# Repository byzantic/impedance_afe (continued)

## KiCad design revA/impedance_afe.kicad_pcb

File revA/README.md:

> **Superseded by Rev B** (repo root). These Rev A files were converted to KiCad 9/10 in commit 697954e.
> The scripts in `revA/scripts/` write KiCad 7 files and would overwrite that conversion. Keep them for reference only.

# Impedance / C-V / DLTS / Electrochem AFE — Rev A (generated)

Fabrication outputs (Gerbers, JLCPCB BOM/CPL, schematic PDF, renders) are attached to each [GitHub Release](../../releases), not stored in the repo.

KiCad 7 format (opens in KiCad 8/9, which will offer to upgrade the files). 2-layer, 150 × 110 mm, 1.6 mm FR4, JLCPCB rules (0.25 mm default track/clearance, 0.6/0.3 mm vias).

## Architecture
| Block | Parts | Function |
|---|---|---|
| Power | J1, D1/D2, FB1/FB2, U8 | External ±15 V (bench supply), Schottky reverse protection, ferrite + bulk filtering, 78M05 → +5 V for relays and logic |
| Drive | J2 → R3 → U1 (OPA828), R4 → J3 (CE) | **Device mode** (K6 on): U1 is a follower, CE = VIN, RE senses the DUT. **Potentiostat** (K7 on, K6 off): PI loop, R5 = 10k, C9 = 100p, R6 = 1k zero, drives CE so that V_RE = VIN |
| RE / guard | J4 → R7 → U2 (electrometer follower), U3 → R9 → J5 and the J4 shell | Driven guard on the RE cable shield and the GUARD BNC; RE_BUF copper guard around U2's input |
| V monitor | R10/R11 (0.1 %) → U4 → J6 | V_OUT = V_RE / 2, back-terminated in 49.9 Ω |
| Hi-gain TIA | J7 (WE) → U5, R21–R25 ∥ C21–C25, K1–K5 | Virtual ground on WE. Ranges 10k / 100k / 1M / 10M / 100M (±5 V full scale = 500 µA … 50 nA). Relays sit on the output side, so off-relay leakage shows up as a gain error, not an offset |
| Lo-gain TIA | D3 (BAV199 antiparallel) → U6, R15 = 499 Ω ∥ 68 p | Above about V_sat/R_f, U5 saturates, WE rises about 0.6 V and the current diverts to U6 (10 mA full scale). Needs no sync and adds no charge injection |
| Control | J10 → U7 (74HCT541) → coils, D11–D18 | High-side coil drive, so off coils sit at 0 V (keeps coil-to-contact leakage out of the summing node) |

Output polarity: I_HI = −I_WE·R_f and I_LO = −I_WE·499 Ω, where I_WE is current flowing *into* the WE terminal.

## GPIO header J10 (3.3 V logic OK; 100k pulls to +5 V or GND)
| Pin | Signal | Relay | Default |
|---|---|---|---|
| 1 | CTL1 | K1 10k range | off |
| 2 | CTL2 | K2 100k | off |
| 3 | CTL3 | K3 1M | **on** |
| 4 | CTL4 | K4 10M | off |
| 5 | CTL5 | K5 100M | off |
| 6 | CTL6 | K6 DEV (follower) | **on** |
| 7 | CTL7 | K7 PSTAT (PI loop) | off |
| 8 | CTL8 | K8 RE_LOCAL (RE tied to CE on the board) | **on** |
| 9, 10 | GND | | |
Exactly one range should be on at a time; use break-before-make, ~2 ms. Keep ≤ 4 coils on at once (74HCT541 Icc limit). For potentiostat mode: CTL6 = 0, CTL7 = 1, CTL8 = 0.

## Verification status
- Netlist: the KiCad-exported netlist was checked against the design intent by script (69 nets, 0 mismatches). **KiCad's own ERC was not run** (KiCad 7 has no headless ERC). Run ERC in KiCad before ordering.
- PCB DRC (KiCad 7): 0 clearance errors, 0 unconnected. The remaining items are cosmetic silkscreen overlaps/edge clips and "footprint not in library table" notices.
- Not simulated. Loop stability (especially the PI potentiostat with a real cell) and the TIA compensation values are first-pass hand calculations.

## Things to check / known limitations
1. **Reed relay pinout** assumes Standex/Meder SIL: pins 1 and 7 are the contact, pins 3 and 5 are the coil. Confirm against the datasheet of the part you buy.
2. Generic SIP-1A05 insulation is specified at only ≥1e10 Ω. That is up to ~1 % gain error on the 100M range (calibrate it out), or fit Coto 9007 / Pickering parts (≥1e12) on K4/K5.
3. During a DLTS fill pulse the WE node sits about 0.6 V off ground (diode drop), so the DUT voltage is lower by that amount while I_LO is active.
4. At 1 MHz C-V, expect a few degrees of phase shift in the V and I chains. Calibrate with reference R/C loads (open/short/load) for C-V.
5. PI compensation (C9/R6) and C26 may need tuning for your cells and cables.
6. Most passives have no LCSC numbers. Use JLC's BOM matcher. Verified: OPA828IDR = C1850247, reed relay = C7316298. The 100 MΩ (R25) and 0.47 pF (C24) values may need sourcing.
7. The BNC footprint is the Amphenol B6252HB right-angle. Check that your BNCs match its pin pattern. JLC CPL rotations for SOT-23/SOIC may need fixing in the JLC preview.
8. The pull-ups go to +5 V. With a 3.3 V MCU high, about 17 µA flows into the GPIO clamp (harmless for most MCUs). Fit 3.3 V-referenced pull-ups if you prefer.
9. The pulse-sync input is not needed with diode steering, so none was fitted.

## Regenerating
Everything comes from `scripts/design.py`. Run the scripts from the repo root with KiCad 7's Python (`pcbnew`) and Freerouting. `route.py` expects the jar at `/root/tools/fr.jar`, so edit that path first.
```
python3 scripts/gen_sch.py          # schematic + sym_uuid.json
kicad-cli sch export netlist -o afe.net impedance_afe.kicad_sch && python3 scripts/check_net.py
PASSES=80 bash scripts/build_pcb.sh # place, pre-route critical nets, autoroute, clean up
```
Note: the autoroute pass is not deterministic. The board in this repo is the checked result; regenerating will change the routing.

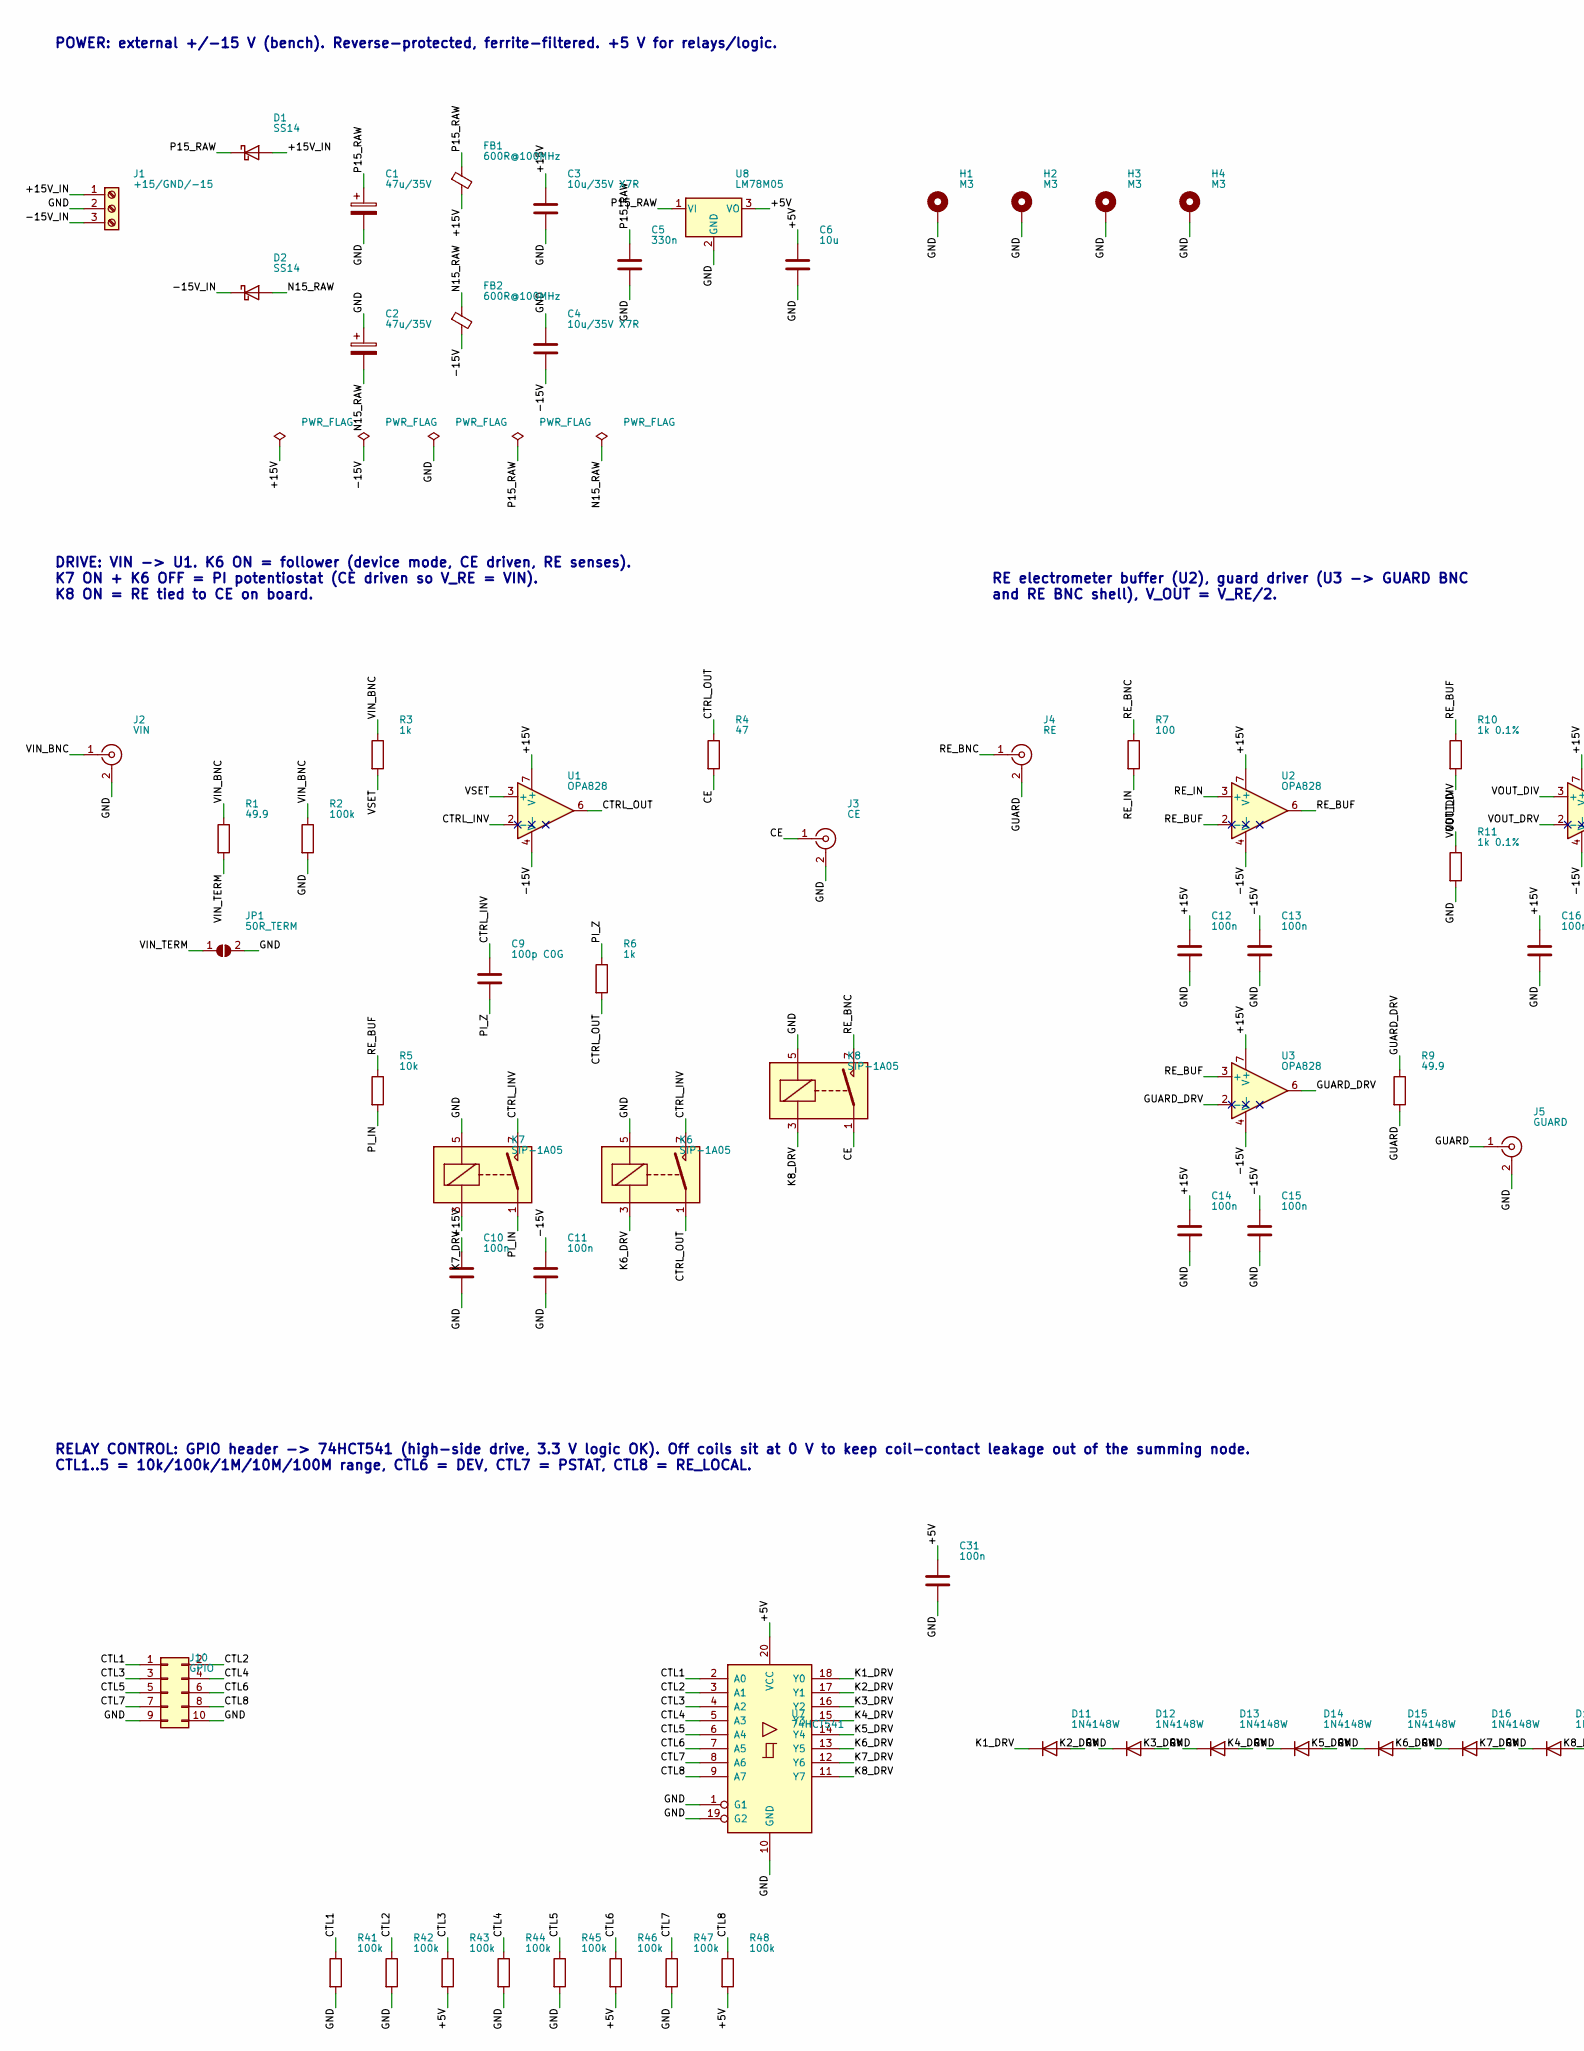
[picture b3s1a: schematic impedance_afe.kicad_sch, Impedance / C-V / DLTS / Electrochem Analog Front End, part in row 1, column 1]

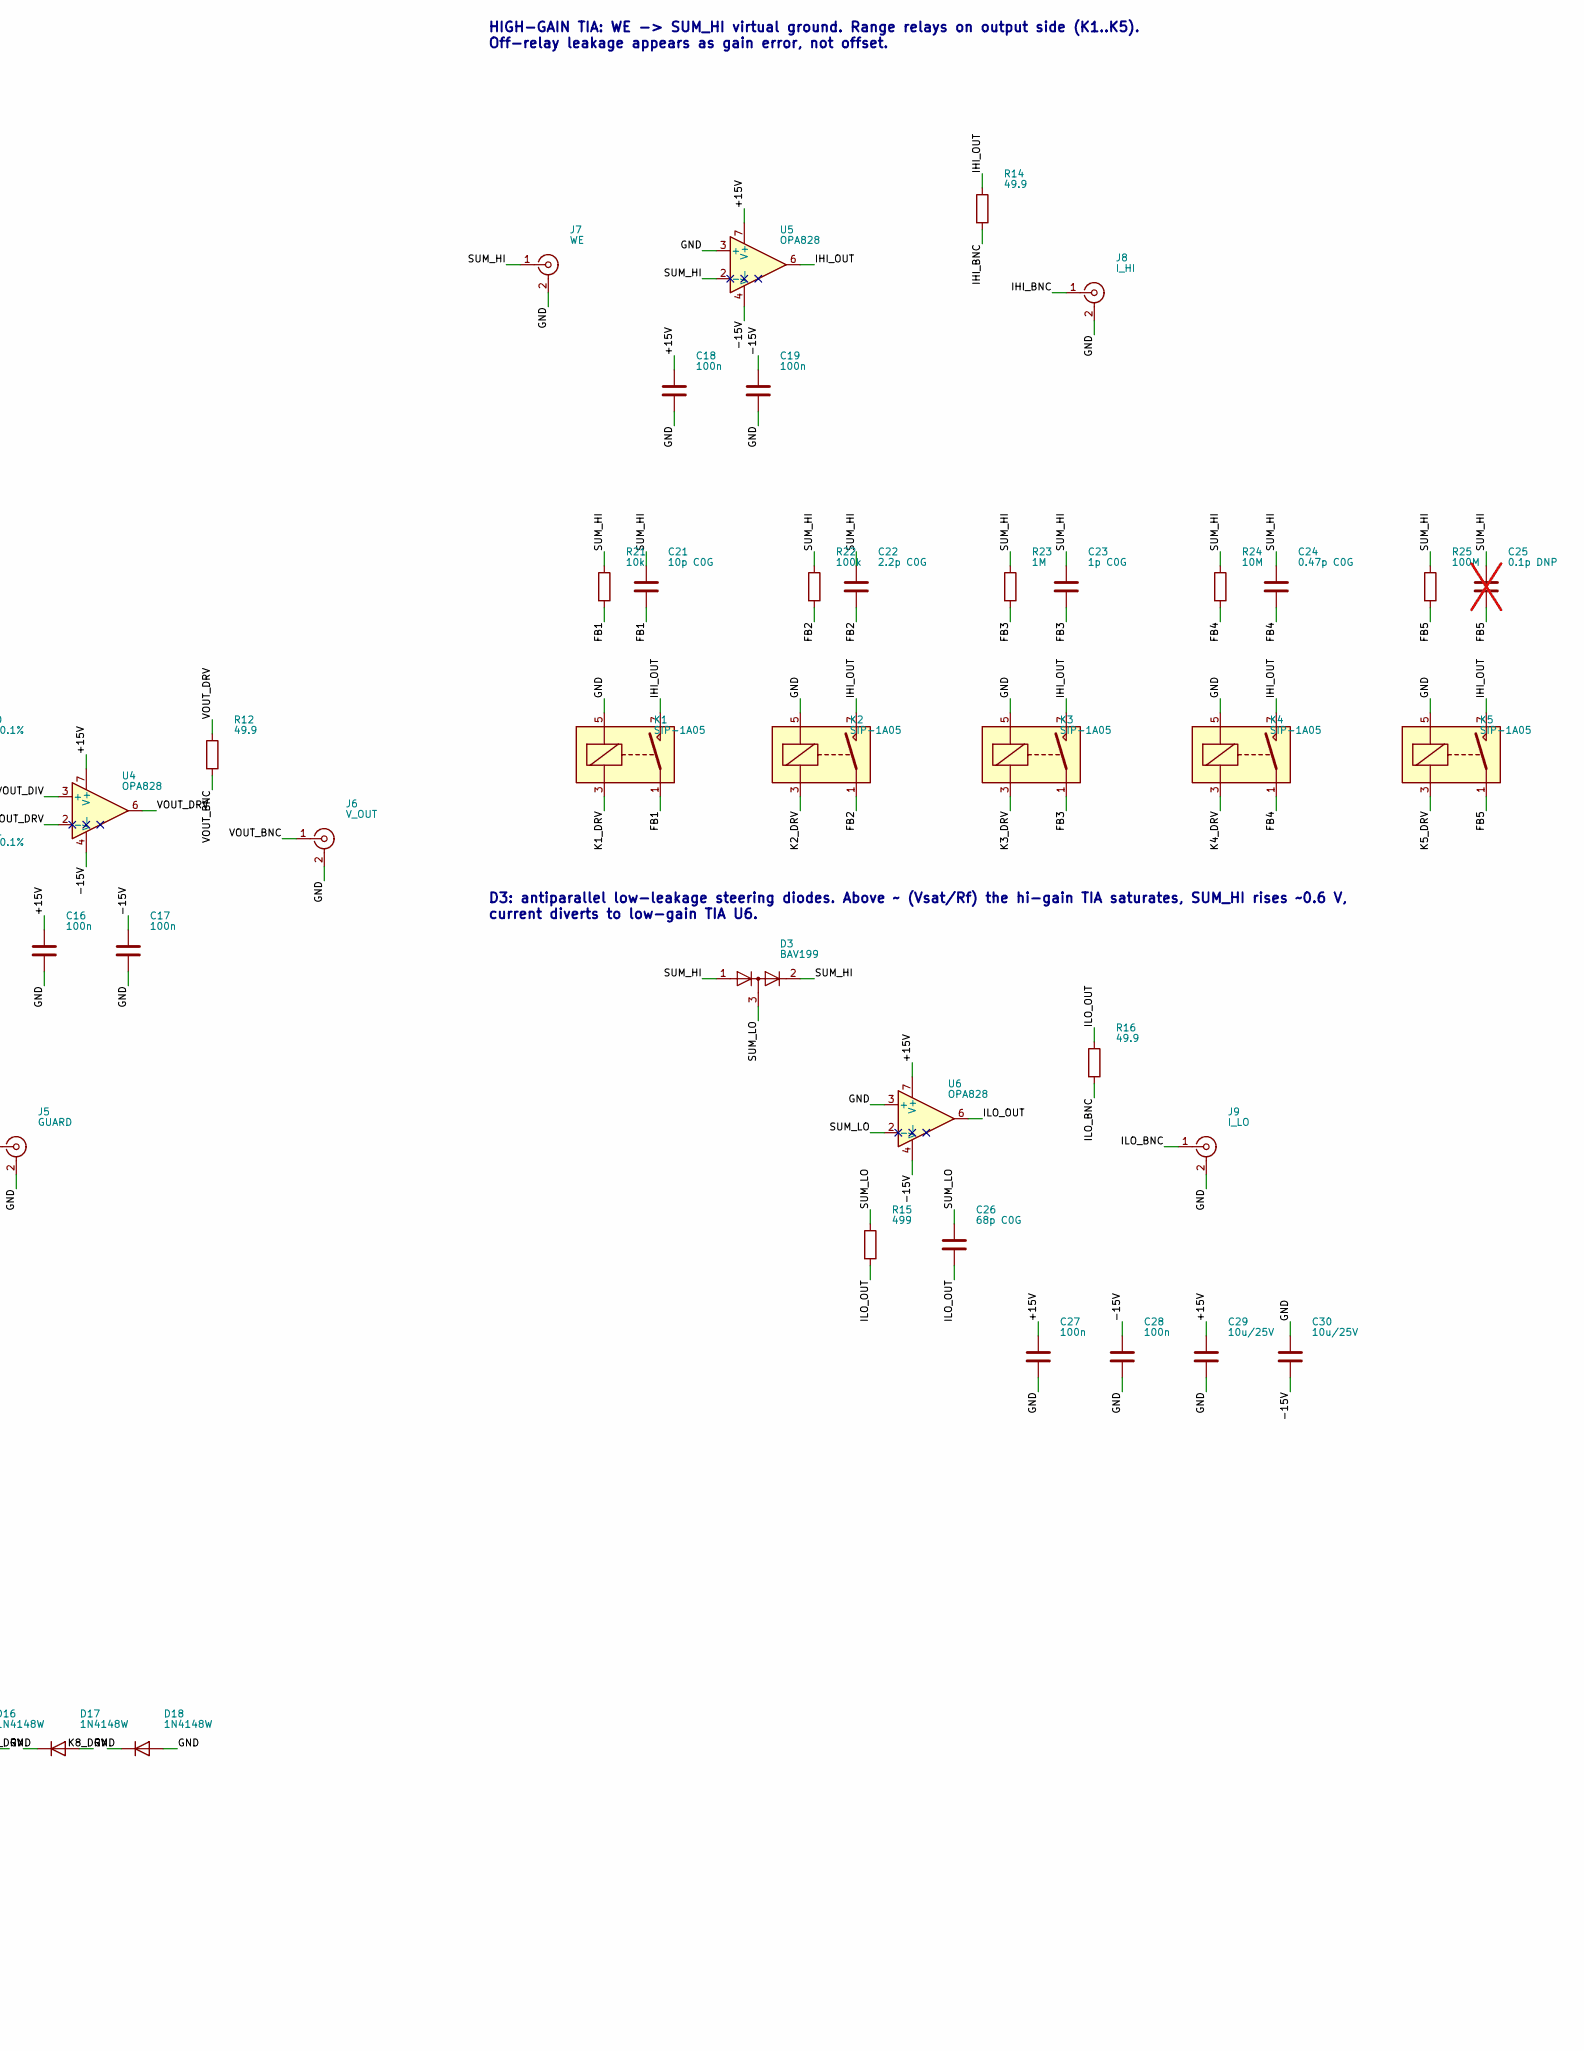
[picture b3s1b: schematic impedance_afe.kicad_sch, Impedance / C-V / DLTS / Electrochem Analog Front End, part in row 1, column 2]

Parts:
C1, C2: 47u/35V; CP_Elec_6.3x7.7
C3, C4: 10u/35V X7R; C_1206_3216Metric
C5: 330n; C_0805_2012Metric
C6: 10u; C_0805_2012Metric
C9: 100p C0G; C_0805_2012Metric
C10, C11, C12, C13, C14, C15, C16, C17, C18, C19, C27, C28, C31: 100n; C_0805_2012Metric
C21: 10p C0G; C_0805_2012Metric
C22: 2.2p C0G; C_0805_2012Metric
C23: 1p C0G; C_0805_2012Metric
C24: 0.47p C0G; C_0805_2012Metric
C25: 0.1p DNP; C_0805_2012Metric; not fitted
C26: 68p C0G; C_0805_2012Metric
C29, C30: 10u/25V; C_1206_3216Metric
D1, D2: SS14; D_SMA; MPN SS14
D3: BAV199; SOT-23; MPN BAV199 (low-leakage, pins1+2 tied -> an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
D11, D12, D13, D14, D15, D16, D17, D18: 1N4148W; D_SOD-123; MPN 1N4148W
FB1, FB2: 600R@100MHz; L_0805_2012Metric
H1, H2, H3, H4: M3; MountingHole_3.2mm_M3_Pad_Via
J1: +15/GND/-15; TerminalBlock_Phoenix_MKDS-1,5-3-5.08_1x03_P5.08mm_Horizont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
J2: VIN; BNC_Amphenol_B6252HB-NPP3G-50_Horizontal; MPN BNC R/A PCB 50R (Amphenol B6252HB-NPP3G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
J3: CE; BNC_Amphenol_B6252HB-NPP3G-50_Horizontal; MPN BNC R/A PCB 50R (Amphenol B6252HB-NPP3G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
J4: RE; BNC_Amphenol_B6252HB-NPP3G-50_Horizontal; MPN BNC R/A PCB 50R (Amphenol B6252HB-NPP3G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
J5: GUARD; BNC_Amphenol_B6252HB-NPP3G-50_Horizontal; MPN BNC R/A PCB 50R (Amphenol B6252HB-NPP3G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
J6: V_OUT; BNC_Amphenol_B6252HB-NPP3G-50_Horizontal; MPN BNC R/A PCB 50R (Amphenol B6252HB-NPP3G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
J7: WE; BNC_Amphenol_B6252HB-NPP3G-50_Horizontal; MPN BNC R/A PCB 50R (Amphenol B6252HB-NPP3G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
J8: I_HI; BNC_Amphenol_B6252HB-NPP3G-50_Horizontal; MPN BNC R/A PCB 50R (Amphenol B6252HB-NPP3G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
J9: I_LO; BNC_Amphenol_B6252HB-NPP3G-50_Horizontal; MPN BNC R/A PCB 50R (Amphenol B6252HB-NPP3G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
J10: GPIO; PinHeader_2x05_P2.54mm_Vertical
JP1: 50R_TERM; SolderJumper-2_P1.3mm_Open_RoundedPad1.0x1.5mm
K1, K2, K3, K4, K5, K6, K7, K8: SIP-1A05; Relay_SPST_StandexMeder_SIL_Form1A; MPN SIP-1A05 (Standex/Meder SIL05-1A72-71 c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; LCSC C7316298
R1, R9, R12, R14, R16: 49.9; R_0805_2012Metric
R2, R22, R41, R42, R43, R44, R45, R46, R47, R48: 100k; R_0805_2012Metric
R3, R6: 1k; R_0805_2012Metric
R4: 47; R_0805_2012Metric
R5, R21: 10k; R_0805_2012Metric
R7: 100; R_0805_2012Metric
R10, R11: 1k 0.1%; R_0805_2012Metric
R15: 499; R_0805_2012Metric
R23: 1M; R_1206_3216Metric
R24: 10M; R_1206_3216Metric
R25: 100M; R_1206_3216Metric
U1, U2, U3, U4, U5, U6: OPA828; SOIC-8_3.9x4.9mm_P1.27mm; MPN OPA828IDR; LCSC C1850247
U7: 74HCT541; SOIC-20W_7.5x12.8mm_P1.27mm; MPN SN74HCT541DWR
U8: LM78M05; TO-252-2; MPN MC78M05CDTRKG

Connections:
+5V: C6.1, C31.1, R43.2, R46.2, R48.2, U7.20 (VCC), U8.3 (VO)
+15V: C3.1, C10.1, C12.1, C14.1, C16.1, C18.1, C27.1, C29.1, FB1.2, U1.7 (V+), U2.7 (V+), U3.7 (V+), U4.7 (V+), U5.7 (V+), U6.7 (V+)
+15V_IN: D1.2 (A), J1.1
-15V: C4.2, C11.1, C13.1, C15.1, C17.1, C19.1, C28.1, C30.2, FB2.2, U1.4 (V-), U2.4 (V-), U3.4 (V-), U4.4 (V-), U5.4 (V-), U6.4 (V-)
-15V_IN: D2.1 (K), J1.3
CE: J3.1 (In), K8.1, R4.2
CTL1: J10.1, R41.1, U7.2 (A0)
CTL2: J10.2, R42.1, U7.3 (A1)
CTL3: J10.3, R43.1, U7.4 (A2)
CTL4: J10.4, R44.1, U7.5 (A3)
CTL5: J10.5, R45.1, U7.6 (A4)
CTL6: J10.6, R46.1, U7.7 (A5)
CTL7: J10.7, R47.1, U7.8 (A6)
CTL8: J10.8, R48.1, U7.9 (A7)
CTRL_INV: C9.1, K6.7, K7.7, U1.2 (-)
CTRL_OUT: K6.1, R4.1, R6.2, U1.6
FB1: C21.2, K1.1, R21.2
FB2: C22.2, K2.1, R22.2
FB3: C23.2, K3.1, R23.2
FB4: C24.2, K4.1, R24.2
FB5: C25.2, K5.1, R25.2
GND: C1.2, C2.1, C3.2, C4.1, C5.2, C6.2, C10.2, C11.2, C12.2, C13.2, C14.2, C15.2, C16.2, C17.2, C18.2, C19.2, C27.2, C28.2, C29.2, C30.1, C31.2, D11.2 (A), D12.2 (A), D13.2 (A), D14.2 (A), D15.2 (A), D16.2 (A), D17.2 (A), D18.2 (A), H1.1, H2.1, H3.1, H4.1, J1.2, J2.2 (Ext), J3.2 (Ext), J5.2 (Ext), J6.2 (Ext), J7.2 (Ext), J8.2 (Ext), J9.2 (Ext), J10.9, J10.10, JP1.2 (B), K1.5, K2.5, K3.5, K4.5, K5.5, K6.5, K7.5, K8.5, R2.2, R11.2, R41.2, R42.2, R44.2, R45.2, R47.2, U5.3 (+), U6.3 (+), U7.1 (G1), U7.10 (GND), U7.19 (G2), U8.2 (GND)
GUARD: J4.2 (Ext), J5.1 (In), R9.2
GUARD_DRV: R9.1, U3.2 (-), U3.6
IHI_BNC: J8.1 (In), R14.2
IHI_OUT: K1.7, K2.7, K3.7, K4.7, K5.7, R14.1, U5.6
ILO_BNC: J9.1 (In), R16.2
ILO_OUT: C26.2, R15.2, R16.1, U6.6
K1_DRV: D11.1 (K), K1.3, U7.18 (Y0)
K2_DRV: D12.1 (K), K2.3, U7.17 (Y1)
K3_DRV: D13.1 (K), K3.3, U7.16 (Y2)
K4_DRV: D14.1 (K), K4.3, U7.15 (Y3)
K5_DRV: D15.1 (K), K5.3, U7.14 (Y4)
K6_DRV: D16.1 (K), K6.3, U7.13 (Y5)
K7_DRV: D17.1 (K), K7.3, U7.12 (Y6)
K8_DRV: D18.1 (K), K8.3, U7.11 (Y7)
N15_RAW: C2.2, D2.2 (A), FB2.1
P15_RAW: C1.1, C5.1, D1.1 (K), FB1.1, U8.1 (VI)
PI_IN: K7.1, R5.2
PI_Z: C9.2, R6.1
RE_BNC: J4.1 (In), K8.7, R7.1
RE_BUF: R5.1, R10.1, U2.2 (-), U2.6, U3.3 (+)
RE_IN: R7.2, U2.3 (+)
SUM_HI: C21.1, C22.1, C23.1, C24.1, C25.1, D3.1 (K), D3.2 (A), J7.1 (In), R21.1, R22.1, R23.1, R24.1, R25.1, U5.2 (-)
SUM_LO: C26.1, D3.3 (K), R15.1, U6.2 (-)
VIN_BNC: J2.1 (In), R1.1, R2.1, R3.1
VIN_TERM: JP1.1 (A), R1.2
VOUT_BNC: J6.1 (In), R12.2
VOUT_DIV: R10.2, R11.1, U4.3 (+)
VOUT_DRV: R12.1, U4.2 (-), U4.6
VSET: R3.2, U1.3 (+)

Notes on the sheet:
HIGH-GAIN TIA: WE -> SUM_HI virtual ground. Range relays on output side (K1..K5). Off-relay leakage appears as gain error, not offset.
DRIVE: VIN -> U1. K6 ON = follower (device mode, CE driven, RE senses). K7 ON + K6 OFF = PI potentiostat (CE driven so V_RE = VIN). K8 ON = RE tied to CE on board.
RELAY CONTROL: GPIO header -> 74HCT541 (high-side drive, 3.3 V logic OK). Off coils sit at 0 V to keep coil-contact leakage out of the summing node. CTL1..5 = 10k/100k/1M/10M/100M range, CTL6 = DEV, CTL7 = PSTAT, CTL8 = RE_LOCAL.
RE electrometer buffer (U2), guard driver (U3 -> GUARD BNC and RE BNC shell), V_OUT = V_RE/2.
POWER: external +/-15 V (bench). Reverse-protected, ferrite-filtered. +5 V for relays/logic.
D3: antiparallel low-leakage steering diodes. Above ~ (Vsat/Rf) the hi-gain TIA saturates, SUM_HI rises ~0.6 V, current diverts to low-gain TIA U6.

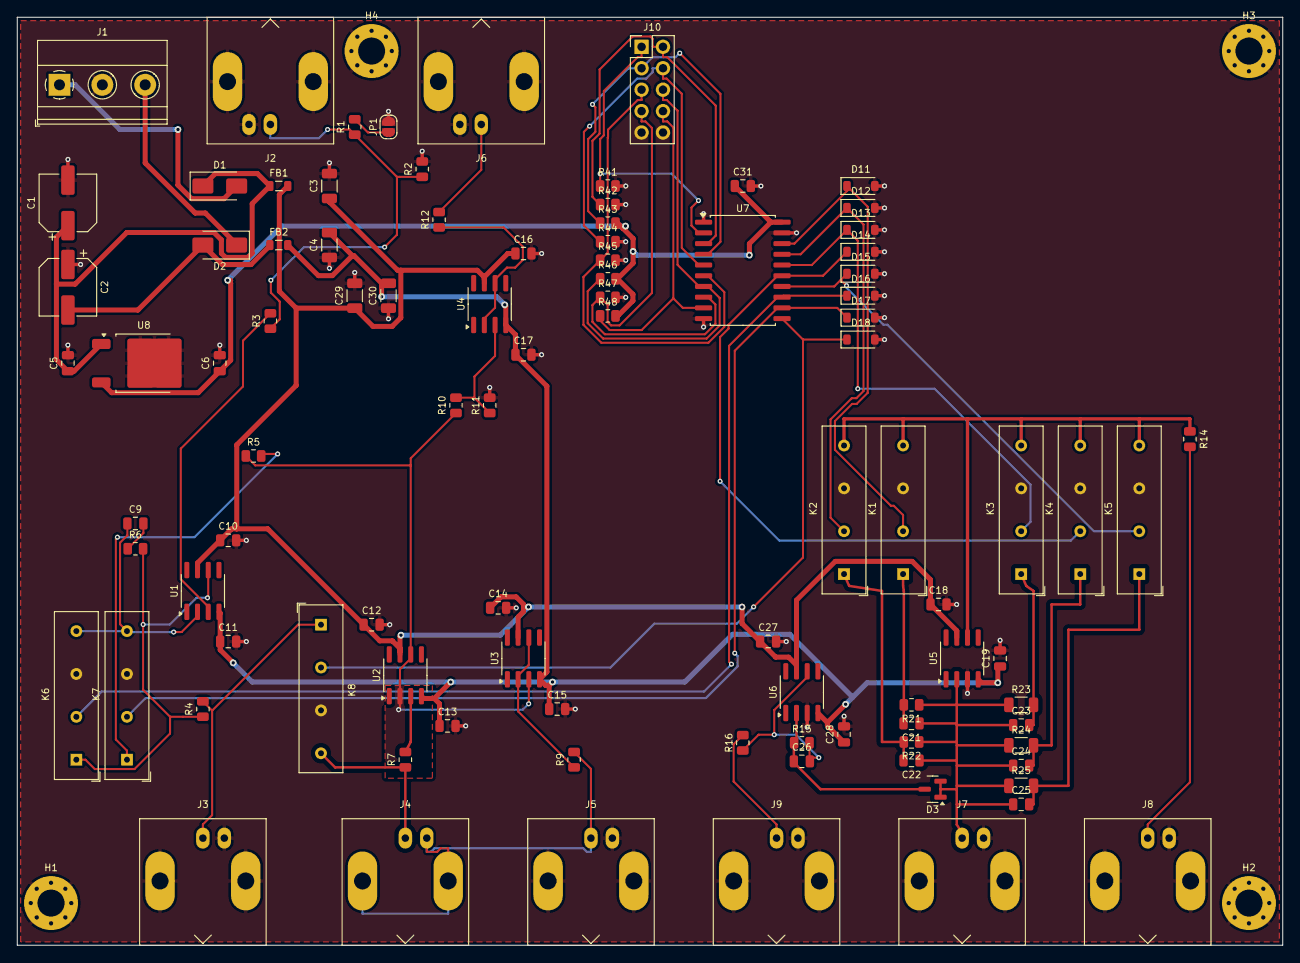
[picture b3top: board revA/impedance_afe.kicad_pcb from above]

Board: 2 copper layers, 150.0 x 110.0 mm, 99 parts (0 on the bottom side), 51 nets.

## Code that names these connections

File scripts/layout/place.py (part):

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put('J11', 190.0, 12.7, 0)     # SYNC_IN, ~23 mm clear of the controller's RJ45

# ================================================================ high-gain TIA (U5) + SUM_HI comb
# U5 rot 90: pin2 (-IN) bottom row, straight above the WE BNC pin.  SUM_HI bus at YBUS runs
# right (ranges, steering transistors) and left (null-injection and cal relays).
WEX = 104.0
UX, UY = WEX + 1.27, YBUS - 8.0
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    put(r, x, YBUS, 90)                                   # pin1 on bus, pin2 up
    put(c, x + (5.0 if long_ else 4.0), YBUS, 90)
    rp = 20.32 if long_ else 10.16
    relay(k, x, YBUS - rp - 4.0, 90)                      # pin1 = FBn, pin7 = IHI_OUT on top
QX = WEX + 74.5
put('Q1', QX, YBUS, 90)              # pins 1,2 SUM_HI (pin1 on bus), pin3 SUM_LO top
put('Q2', QX + 5.0, YBUS - 2.54, 270)  # pin3 SUM_HI on bus, pins 1,2 SUM_LO
# left branch: null injection relays nearest U5, cal relays further left (pin7 = SUM_HI on bus, pin1 up)
DX = UX - 105.27                     # left branch kept rigid relative to U5
relay('K16', 97.2 + DX, YBUS - 15.24, 270)
relay('K15', 90.8 + DX, YBUS - 15.24, 270)
relay('K13', 76.4 + DX, YBUS - 15.24, 270)
relay('K11', 70.0 + DX, YBUS - 15.24, 270)
put('R18', 70.0 + DX, YBUS - 15.24 - 14.2, 270)           # pin1 CE_INT top, pin2 CALR_MID bottom
put('C16', 73.2 + DX, YBUS - 15.24 - 6.1, 270)            # pin1 CE_INT top, pin2 CALC_MID bottom
relay('K12', 70.0 + DX, YBUS - 15.24 - 18.6, 90)          # NC to GND, pin1 CALR_MID bottom
relay('K14', 76.4 + DX, YBUS - 15.24 - 10.8, 90)          # NC to GND, pin1 CALC_MID bottom
put('C18', 90.8 + DX, YBUS - 15.24 - 6.1, 270)            # NULLC_DRV top -> NULLC_INJ bottom
relay('K17', 83.6 + DX, YBUS - 15.24 - 20.8, 270)         # pin1 NULLC_R top, pin7 NULLC_INJ bottom
put('R30', 97.2 + DX, YBUS - 15.24 - 14.4, 270)           # NULLG_AC top -> NULLG_INJ bottom
relay('K18', 102.6 + DX, YBUS - 15.24 - 20.8, 270)        # pin1 NULLG_R top, pin7 NULLG_INJ bottom
put('C19', 83.6 + DX, 89.4, 270)                          # NULLC_DRV top -> NULLC_R bottom (K17 pin1)
put('R31', 95.0 + DX, 91.3, 0)                            # NULLG_AC -> NULLG_R (K18 pin1)
put('C20', 97.5 + DX, 87.8, 0)                            # NULLG_DRV -> NULLG_AC (film)
opamp('U13', 90.0 + DX, 80.0)
opamp('U14', 112.0 + DX, 80.0)
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put('C17', 160.0 + VM, 89.0, 0); put('R23', 159.0 + VM, 92.5, 0)
put('R24', 185.0 + VM, 80.0, 0)
put('R25', 210.0 + VM, 86.0, 0); put('R27', 210.0 + VM, 89.5, 0)
relay('K19', 234.0, 100.0, 270)      # NC: VDC_R -> VOUT (pin7 bottom, toward J8)
relay('K20', 240.4, 100.0, 270)      # VAC_R -> VOUT

# ================================================================ RE electrometer / guard / RE_MON
U2X, U2Y = RE_X - 1.27, YBUS - 15.5
opamp('U2', U2X, U2Y, 'R')
put('R19', RE_X, YBUS + 1.4, 90)     # pin1 RE_BNC (bottom, by J5), pin2 RE_IN up to U2 pin3
opamp('U3', RE_X + 9.0, 102.0)
opamp('U7', RE_X + 9.0, 86.0)
put('R20', RE_X + 12.0, YBUS - 9.0, 270)    # GUARD_DRV top -> GUARD bottom (J6, J5 shell)
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put('FB1', 3.0, 31.0, 0); put('FB2', 3.0, 34.5, 0)
put('C3', 18.0, 34.0, 0); put('C4', 26.0, 34.0, 0)
put('U25', 30.0, 4.0, 180)           # heatsink area kept clear below (y 6..20, x 21..34)
put('C5', 35.2, 1.8, 270);                 # input cap upright beside pin 1 (P15_RAW)
put('C6', 33.0, 26.0, 0); put('C7', 33.0, 34.0, 0)

# ================================================================ shift registers, pulls, relay drivers (back edge)
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SLOTX = [80.5 + 3.2 * j for j in range(8)] + [106.0 + 3.2 * j for j in range(8)]
for m in range(16):                  # R(60+m) belongs to channel m, whose input is CTL(15-m) -> slot 15-m
    put(f'R{60+m}', SLOTX[15 - m], 24.0 + SB, 90)
put('U27', SLOTX[1] + 1.98, 9.62 + SB, 90)    # CTL0..7; pin 1 (QB) over slot 1
put('U28', SLOTX[9] + 1.98, 9.62 + SB, 90)    # CTL8..15
put('C62', 107.3, 9.6 + SB, 90); put('C63', 132.0, 9.6 + SB, 90)
put('R76', 134.8, 13.0 + SB, 90)     # RLY_OE pull-up
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A1Y = 27.0 + 18.5
put('A1', 148.0, A1Y, 0)
ESP_END = A1Y + 28.8                       # ESP32-S3-ETH far end (microSD inserted from here)
# ground link: FB5 / JP5 straddle the bottom-left corner of the controller ground island (pin1 PICO_GND inside)
ISLAND_Y = ESP_END + 1.2
put('FB5', 134.2, ISLAND_Y - 9.5, 270)
put('JP5', 131.0, ISLAND_Y - 2.0, 270)
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

put('J16', *hat_xy(8.37, 4.77), 0)       # PinHeader 2x20 (male): pin1 odd row, even pins outboard
put('J17', *hat_xy(J2X0, 27.5), 0)       # PinHeader 1x12 (male), one column; pin 1 = ADC0P (top)
for i, (X, Y) in enumerate([(3.5, 3.5), (61.5, 3.5), (3.5, 26.5), (61.5, 26.5)]):
    put(f'H{10+i}', *hat_xy(X, Y))

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
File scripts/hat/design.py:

"""ADC/DAC HAT (adc_hat/): net record of intent, read by check.py and the BOM.

Raspberry Pi Zero pHAT outline (65 x 30 mm). Plugs onto J16/J17 of the AFE main board, stacks on a Pi Zero, or runs
from any MCU through the 2x6 edge header J3. J2 (1x12 analog row) takes a socket on the bottom (AFE) or 2.54 mm screw
terminals on top. All SMD parts on top (JLC assembly); J1/J2/J3 and the optional DIP-8 Y1 are hand-soldered.

ADS131M04: AVDD from its own LDO (U3, from 5 V), DVDD/IO = host 3V3. Clock: JP1 1-2 (default) = host GPIO4
(GPCLK0 on a Pi, Pico GP21 on the main board), 2-3 = on-board 8.192 MHz oscillator Y1 (DNP by default).
DAC80502 (dual): VDD = filtered 5 V (+5VA), internal reference, RSTSEL pulled to VDD by R6 (midscale at power-on); VOUTA, VOUTB and
VREFIO go to J2. SPI2C low = SPI (datasheet SBAS793A), the R2 default; JP2 bridged = I2C.
"""
parts = []


def P(ref, sym, value, fp, nets, mpn='', lcsc='', dnp=False, note=''):
    parts.append(dict(ref=ref, sym=sym, value=value, fp=fp, nets={str(k): v for k, v in nets.items()},
                      mpn=mpn, lcsc=lcsc, dnp=dnp, note=note, board=True))


R06 = 'Resistor_SMD:R_0603_1608Metric'
C06 = 'Capacitor_SMD:C_0603_1608Metric'
C08 = 'Capacitor_SMD:C_0805_2012Metric'


# JLC Basic-library parts (checked on jlcpcb.com parts search, 2026-11-21)
L1U, L100N, L220N, L10U = 'C15849', 'C14663', 'C21120', 'C15850'       # 0603 1u 50V X5R, 0603 100n X7R, 0603 220n X7R, 0805 10u 25V
L33R, L10K, L49R9, LFB = 'C23140', 'C25804', 'C23185', 'C1002'         # 0603 1 % 33R, 10k, 49.9R; 0603 600R@100MHz bead


def R(ref, v, a, b, **k): P(ref, 'Device:R', v, R06, {1: a, 2: b}, **k)
def C(ref, v, a, b, fp=C06, **k): P(ref, 'Device:C', v, fp, {1: a, 2: b}, **k)


# Raspberry Pi 40-pin header (socket on the bottom side). Same pin use as the main board's J16.
PI = {1: '+3V3', 17: '+3V3', 2: '+5V', 4: '+5V', 19: 'MOSI', 21: 'MISO', 23: 'SCLK', 24: 'CS_ADC', 26: 'CS_DAC',
      7: 'CLK_IN', 18: 'SYNC', 22: 'DRDY', **{n: 'GND' for n in (6, 9, 14, 20, 25, 30, 34, 39)}}
P('J1', 'Connector_Generic:Conn_02x20_Odd_Even', 'Pi 40-pin', 'Connector_PinSocket_2.54mm:PinSocket_2x20_P2.54mm_Vertical',
  PI, mpn='2x20 female 2.54 mm, 8.5 mm (Pi HAT stacking height)', note='bottom side; ID_SD/ID_SC (27/28) unused')
# single row along the bottom edge, pin 1 at the left (top view): channel pairs P,N, then DAC_OUTB, DAC_OUT (A), DAC_REF, GND
AN = {1: 'IN0P', 2: 'IN0N', 3: 'IN1P', 4: 'IN1N', 5: 'IN2P', 6: 'IN2N', 7: 'IN3P', 8: 'IN3N',
      9: 'DAC_OUTB', 10: 'DAC_OUT', 11: 'DAC_REF', 12: 'GND'}
P('J2', 'Connector_Generic:Conn_01x12', 'Analog', 'Connector_PinSocket_2.54mm:PinSocket_1x12_P2.54mm_Vertical',
  AN, mpn='1x12 female 2.54 mm, 8.5 mm (AFE) or 2.54 mm screw terminals (general use)',
  note='AFE: socket on the bottom, mates main-board J17 (INnN tied to GND there; its pin 9 is unconnected); general use: screw terminals on top')
# MCU / cable header on the right-hand short edge (2x6, IDC-ribbon compatible)
P('J3', 'Connector_Generic:Conn_02x06_Odd_Even', 'SPI', 'Connector_PinHeader_2.54mm:PinHeader_2x06_P2.54mm_Vertical',
  {1: '+5V', 2: 'GND', 3: '+3V3', 4: 'GND', 5: 'SCLK', 6: 'MOSI', 7: 'MISO', 8: 'CS_ADC', 9: 'CS_DAC', 10: 'DRDY',
   11: 'SYNC', 12: 'CLK_IN'}, mpn='2x6 pin header 2.54 mm', note='host supplies 5 V (DAC, AVDD LDO) and 3.3 V logic')

P('U1', 'afe:ADS131M04_PW', 'ADS131M04IPWR', 'Package_SO:TSSOP-20_4.4x6.5mm_P0.65mm',
  {1: '+3V3A', 2: 'GND', 3: 'AIN0P', 4: 'AIN0N', 5: 'AIN1N', 6: 'AIN1P', 7: 'AIN2P', 8: 'AIN2N', 9: 'AIN3N', 10: 'AIN3P',
   20: '+3V3', 19: 'GND', 18: 'ADC_CAP', 17: 'ADC_CLK', 16: 'MOSI', 15: 'MISO', 14: 'SCLK', 12: 'CS_ADC', 13: 'DRDY',
   11: 'SYNC'}, mpn='ADS131M04IPWR', lcsc='C2862562')
for ch in range(4):
    R(f'R{10+2*ch}', '49.9', f'IN{ch}P', f'AIN{ch}P', lcsc=L49R9, note='input filter')
    R(f'R{11+2*ch}', '49.9', f'IN{ch}N', f'AIN{ch}N', lcsc=L49R9, note='input filter')
    C(f'C{11+ch}', '1n C0G', f'AIN{ch}P', f'AIN{ch}N', lcsc='C106246', mpn='CC0603JRNPO9BN102',
      note='differential AA cap (~1.6 MHz with 2x49.9); C0G (JLC extended: no basic C0G 1n)')
C('C2', '1u', '+3V3A', 'GND', lcsc=L1U, note='LDO output'); C('C3', '100n', '+3V3A', 'GND', lcsc=L100N, note='AVDD')
C('C4', '100n', '+3V3', 'GND', lcsc=L100N, note='DVDD'); C('C5', '1u', '+3V3', 'GND', lcsc=L1U, note='DVDD')
C('C6', '220n', 'ADC_CAP', 'GND', lcsc=L220N, note='ADC CAP pin')

P('U3', 'Regulator_Linear:LP5907MFX-3.3', 'LP5907MFX-3.3', 'Package_TO_SOT_SMD:SOT-23-5',
  {1: '+5V', 3: '+5V', 2: 'GND', 5: '+3V3A'}, mpn='LP5907MFX-3.3/NOPB', lcsc='C80670', note='AVDD LDO, low noise')
C('C1', '1u', '+5V', 'GND', lcsc=L1U, note='LDO input'); C('C15', '10u', '+5V', 'GND', fp=C08, lcsc=L10U, note='5 V entry bulk')

# clock
P('Y1', 'Oscillator:ASE-xxxMHz', '8.192MHz', 'afe:Oscillator_DIP-8_ASE-3.2x2.5_Combo',
  {1: '+3V3', 2: 'GND', 3: 'XO_OUT', 4: '+3V3'}, dnp=True,
  mpn='8.192 MHz 3.3 V CMOS XO: DIP-8 half-size can, or 3.2 x 2.5 mm SMD (TBD)',
  note='fit ONE package and set JP1 2-3 when the host gives no clock')
C('C10', '100n', '+3V3', 'GND', lcsc=L100N, note='Y1 decoupling')
R('R1', '33', 'XO_OUT', 'XO_CLK', lcsc=L33R, note='Y1 source termination')
P('JP1', 'Jumper:SolderJumper_3_Bridged12', 'CLK SRC', 'Jumper:SolderJumper-3_P1.3mm_Bridged12_RoundedPad1.0x1.5mm',
  {1: 'CLK_IN', 2: 'ADC_CLK', 3: 'XO_CLK'}, note='1-2 (default) = host GPIO4; 2-3 = Y1')

# DAC
P('U2', 'afe:DAC80502_DRX', 'DAC80502DRX', 'Package_SON:Texas_DRX_WSON-10_2.5x2.5mm_P0.5mm',
  {1: '+5VA', 4: 'GND', 5: 'DAC_SPI2C', 3: 'RSTSEL', 2: 'DAC_OUT', 9: 'DAC_OUTB', 10: 'DAC_REF', 6: 'SCLK', 7: 'CS_DAC',
   8: 'MOSI'}, mpn='DAC80502DRXR', lcsc='C1880990', note='RSTSEL (3) high via R6: both outputs at midscale on power-up')
P('FB1', 'Device:FerriteBead', '600R@100MHz', 'Inductor_SMD:L_0603_1608Metric', {1: '+5V', 2: '+5VA'},
  lcsc=LFB, note='DAC supply filter')
C('C7', '100n', '+5VA', 'GND', lcsc=L100N, note='DAC VDD'); C('C8', '10u', '+5VA', 'GND', fp=C08, lcsc=L10U, note='DAC VDD')
C('C9', '220n', 'DAC_REF', 'GND', lcsc=L220N, note='VREFIO (datasheet: 150 nF minimum)')
R('R2', '10k', 'DAC_SPI2C', 'GND', lcsc=L10K, note='SPI2C low = SPI')
P('JP2', 'Jumper:SolderJumper_2_Open', 'SPI2C HI', 'Jumper:SolderJumper-2_P1.3mm_Open_RoundedPad1.0x1.5mm',
  {1: 'DAC_SPI2C', 2: '+5VA'}, note='bridge for I2C mode (SPI2C high)')
R('R6', '10k', 'RSTSEL', '+5VA', lcsc=L10K, note='RSTSEL high = midscale at power-up; to GND for zero scale')

# host-absent defaults
R('R3', '10k', 'CS_ADC', '+3V3', lcsc=L10K); R('R4', '10k', 'CS_DAC', '+3V3', lcsc=L10K); R('R5', '10k', 'SYNC', '+3V3', lcsc=L10K)

for i in range(4):
    P(f'H{i+1}', 'Mechanical:MountingHole', 'M2.5', 'MountingHole:MountingHole_2.7mm_M2.5', {})

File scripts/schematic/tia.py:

"""Redraw the TIA block (U5 high-gain TIA with K1..K6 range ladder, Q1/Q2 steering, U6 low-gain TIA) fully wired."""
from redraw import *  # noqa

REFS = (['J7', 'U5', 'R32', 'J9', 'Q1', 'Q2', 'U6', 'R33', 'C27', 'R34', 'J10'] +
        [f'R{40+i}' for i in range(1, 7)] + [f'C{40+i}' for i in range(1, 7)] + [f'K{i}' for i in range(1, 7)])


def F(s, ref, ref_xy, val_xy, just='left'):
    """place Reference/Value at absolute points, horizontal text (field angle compensates symbol rotation)"""
    r = s.at(s.sym(ref))[2] % 360
    a = (-r) % 360 if r in (90, 270) else 0
    if r == 180:                       # KiCad mirrors the justification of 180-degree symbols
        just = {'left': 'right', 'right': 'left'}.get(just, just)
    s.field_at(ref, 'Reference', *ref_xy, angle=a, justify=just)
    s.field_at(ref, 'Value', *val_xy, angle=a, justify=just)


def draw(s):
    strip(s, REFS)
    d = Drawing(s)
    Y_IHI, Y_SUM = 45.72, 86.36
    X0, PITCH = 609.6, 30.48

    # ---------------- range ladder: relay contact -> FBn -> Rf || Cf -> SUM_HI
    cols = []
    for i in range(6):
        xk = X0 + PITCH * i
        k, r, c = f'K{i+1}', f'R{41+i}', f'C{41+i}'
        s.move(k, xk, 58.42, 0)
        xr, xc = xk + 5.08, xk + 12.7
        s.move(r, xr, 78.74, 180)      # pin2 (FBn) top, pin1 (SUM_HI) bottom
        s.move(c, xc, 78.74, 180)
        p7, p1, p5, p3 = (s.pin(k, n) for n in (7, 1, 5, 3))
        d.w(p7, (p7[0], Y_IHI))
        d.w(p1, (p1[0], 71.12), (xc, 71.12), s.pin(c, 2))
        d.w((xr, 71.12), s.pin(r, 2))
        d.w(s.pin(r, 1), (xr, Y_SUM)); d.w(s.pin(c, 1), (xc, Y_SUM))
        d.w(p5, (p5[0], 48.26), (xk - 10.16, 48.26))
        s.power('power:GND', 'GND', xk - 10.16, 48.26)
        d.w(p3, (p3[0], 67.31))
        s.label(f'KD{i}', p3[0], 67.31, 270)
        s.label(f'FB{i+1}', xr + 1.27, 71.12, 0)
        cols.append((xr, xc))

    # ---------------- U5 high-gain TIA, WE BNC
    s.move('U5', 609.6, 106.68, 0)
    XS = 594.36                                        # SUM_HI riser
    XO = 787.4                                         # output riser
    u2, u3, u6 = s.pin('U5', 2), s.pin('U5', 3), s.pin('U5', 6)
    d.w((XS, Y_SUM), (cols[-1][1], Y_SUM))
    d.w((XS, Y_SUM), (XS, u2[1]), u2)
    d.w(u3, (u3[0] - 2.54, u3[1])); s.power('power:GND', 'GND', u3[0] - 2.54, u3[1])
    s.power('power:+15V', '+15V', *s.pin('U5', 7))
    s.power('power:-15V', '-15V', *s.pin('U5', 4), 180)
    for n in (1, 5, 8):
        s.no_connect(*s.pin('U5', n))
    s.move('J7', XS, 124.46, 270)                      # pin1 up, shield left
    d.w((XS, u2[1]), s.pin('J7', 1))
    js = s.pin('J7', 2); d.w(js, (js[0], js[1])); s.power('power:GND', 'GND', *js)
    d.w((XS, Y_SUM), (XS - 7.62, Y_SUM)); s.label('SUM_HI', XS - 7.62, Y_SUM, 180)
    # output: right under the ladder, up to the IHI_OUT bus; R32 -> I_HI BNC
    d.w(u6, (XO, u6[1]), (XO, Y_IHI), (X0 + 5.08, Y_IHI))
    d.w((XO, Y_IHI), (XO + 7.62, Y_IHI)); s.label('IHI_OUT', XO + 7.62, Y_IHI, 0)
    s.move('R32', 797.56, u6[1], 90)
    s.move('J9', 816.61, u6[1], 0)
    d.w((XO, u6[1]), s.pin('R32', 1)); d.w(s.pin('R32', 2), s.pin('J9', 1))
    s.label('IHI_BNC', s.pin('R32', 2)[0] + 1.27, u6[1], 0)
    s.power('power:GND', 'GND', *s.pin('J9', 2))

    # ---------------- Q1/Q2 C-B junctions (B+E tied), anti-parallel between SUM_HI and SUM_LO
    # 2N3904 pins: 1 = E, 2 = B, 3 = C.  Q1: B,E = SUM_HI, C = SUM_LO.  Q2: B,E = SUM_LO, C = SUM_HI.
    Y_HI, Y_LO = 132.08, 147.32
    s.move('Q1', 614.68, 137.16, 180)      # E top, C bottom, B right
    s.move('Q2', 637.54, 137.16, 0)        # C top, E bottom, B left
    XB = 599.44
    d.w((XB, u2[1]), (XB, Y_HI), s.pin('Q2', 3))
    qb = s.pin('Q1', 2); d.w(qb, (qb[0] + 2.54, qb[1]), (qb[0] + 2.54, Y_HI))
    d.w(s.pin('Q1', 3), (s.pin('Q1', 3)[0], Y_LO))
    d.w(s.pin('Q2', 1), (s.pin('Q2', 1)[0], Y_LO))
    qb = s.pin('Q2', 2); d.w(qb, (qb[0] - 2.54, qb[1]), (qb[0] - 2.54, Y_LO))

    # ---------------- U6 low-gain TIA, R33 || C27, R34 -> I_LO BNC
    s.move('U6', 670.56, 144.78, 0)
    v2, v3, v6 = s.pin('U6', 2), s.pin('U6', 3), s.pin('U6', 6)
    d.w((s.pin('Q1', 3)[0], Y_LO), v2)
    s.label('SUM_LO', 647.7, Y_LO, 0)
    d.w(v3, (v3[0] - 2.54, v3[1])); s.power('power:GND', 'GND', v3[0] - 2.54, v3[1])
    s.power('power:+15V', '+15V', *s.pin('U6', 7))
    s.power('power:-15V', '-15V', *s.pin('U6', 4), 180)
    for n in (1, 5, 8):
        s.no_connect(*s.pin('U6', n))
    XL, XR = 655.32, 683.26
    s.move('R33', 668.02, 160.02, 90)
    s.move('C27', 668.02, 167.64, 90)
    d.w((XL, Y_LO), (XL, 167.64), s.pin('C27', 1)); d.w((XL, 160.02), s.pin('R33', 1))
    d.w(s.pin('C27', 2), (XR, 167.64), (XR, v6[1])); d.w(s.pin('R33', 2), (XR, 160.02))
    d.w(v6, (XR, v6[1]))
    s.move('R34', 693.42, v6[1], 90)
    s.move('J10', 712.47, v6[1], 0)
    d.w((XR, v6[1]), s.pin('R34', 1)); d.w(s.pin('R34', 2), s.pin('J10', 1))
    s.label('ILO_BNC', s.pin('R34', 2)[0] + 1.27, v6[1], 0)
    s.power('power:GND', 'GND', *s.pin('J10', 2))
    d.w((XR, 167.64), (XR, 172.72)); s.label('ILO_OUT', XR, 172.72, 270)


    # ---------------- field placement
    for i in range(6):
        xk = X0 + PITCH * i
        xr, xc = cols[i]
        F(s, f'K{i+1}', (xk - 8.89, 57.15), (xk - 8.89, 59.69), 'right')
        F(s, f'R{41+i}', (xr - 2.54, 73.66), (xr - 2.54, 76.2), 'right')
        F(s, f'C{41+i}', (xc + 2.54, 80.01), (xc + 2.54, 82.55), 'left')
    F(s, 'J7', (XS + 3.81, 123.19), (XS + 3.81, 125.73), 'left')
    F(s, 'Q1', (609.6, 139.7), (609.6, 142.24), 'right')
    F(s, 'Q2', (642.62, 129.54), (642.62, 132.08 - 4.0), 'left')
    F(s, 'U6', (671.83, 134.62), (671.83, 137.16), 'left')
    F(s, 'R32', (795.02, 101.6), (795.02, 104.14), 'left')
    F(s, 'R34', (690.88, 139.7), (690.88, 142.24), 'left')
    F(s, 'R33', (662.94, 163.83), (670.56, 163.83), 'left')
    F(s, 'C27', (662.94, 171.45), (670.56, 171.45), 'left')

    d.pins_of(REFS)
    return d.emit()


if __name__ == '__main__':
    s = Sch()
    print('wires', draw(s))
    s.save()

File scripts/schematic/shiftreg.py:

"""One-off: relay lines from 2x 74HC595 on SPI instead of 16 Pico GPIOs (Pico 2 / ESP32-S3-ETH compatible pin map).

Adds U27/U28 (74HC595), R76 (RLY_OE pull-up), C62/C63; removes J12 (CTL fallback header); J13 becomes a 2x8
right-angle box header carrying RLY_LATCH/RLY_OE too; re-terminates A1 (new pin map) and J17 (signals on the
even row).  Nets come from scripts/design.py.
"""
from redraw import *  # noqa
from hat_split import prune


def main():
    s = Sch()
    for ref in ('J12', 'J13'):
        strip(s, [ref])
        s.remove(s.sym(ref))
    s.add_symbol('Connector_Generic:Conn_02x08_Odd_Even', 'J13', 'SPI/AUX', 'Connector_IDC:IDC-Header_2x08_P2.54mm_Horizontal',
                 693.42, 454.66, 0, {'MPN': '2x8 shrouded box header, right angle',
                                     'Note': 'external SPI master port: HAT and relays with the controller absent or in reset'})
    s.add_symbol('74xx:74HC595', 'U27', '74HC595', 'Package_DIP:DIP-16_W7.62mm_Socket', 523.24, 452.12, 0)
    s.add_symbol('74xx:74HC595', 'U28', '74HC595', 'Package_DIP:DIP-16_W7.62mm_Socket', 574.04, 452.12, 0,
                 {'Note': 'QH (pin 9) unused'})
    s.add_symbol('Device:R', 'R76', '10k', design.FP['R'], 607.06, 441.96, 0,
                 {'Note': '595 outputs off (Hi-Z) until firmware drives RLY_OE low'})
    s.add_symbol('Device:C', 'C62', '100n', design.FP['C'], 607.06, 469.9, 0)
    s.add_symbol('Device:C', 'C63', '100n', design.FP['C'], 619.76, 469.9, 0)
    s.set_prop('A1', 'Footprint', 'afe:Pico2_ESP32-S3-ETH_THT')
    s.set_prop('A1', 'Value', 'Pico 2 / ESP32-S3-ETH')
    s.set_prop('A1', 'MPN', 'SC1631 (Pico 2) or Waveshare ESP32-S3-ETH, on 2x 1x20 sockets')

    b = Block(s, ['A1', 'J17', 'J13', 'U27', 'U28', 'R76', 'C62', 'C63'])
    for ref in ('U27', 'U28'):
        x, y, _ = s.at(s.sym(ref))
        b.F(ref, (x + 2.54, y - 16.51), (x + 2.54, y - 13.97))
    for n in (3, 8, 13, 18, 23, 28, 33, 38):   # GND pins: symbol clear of the signal labels
        b.term('A1', n, 17.78)
    b.finish()
    prune(s)

    for t in s.items('text'):
        v = val(t)
        if v.startswith('CONTROL: Pico 2'):
            t[1] = S('CONTROL: Pico 2 or Waveshare ESP32-S3-ETH (socketed; same header pins) -> SPI -> U27/U28 74HC595 -> CTL0..15 -> '
                     '2x TBD62783A high-side drivers -> relay coils.\\n'
                     'U27 QA..QH = CTL0..7, U28 QA..QH = CTL8..15 (MOSI -> U27 -> U28). Driver channel m (KDm) is driven by CTL(15-m); '
                     'the order is for routing, firmware maps it.\\n'
                     'RLY_OE is pulled high (595 outputs Hi-Z) until firmware loads the latches and drives it low; the 4.7k pulls set '
                     'the power-up state: ON = CTL3 (1M), CTL6 (DEV), CTL8 (RE_LOCAL).\\n'
                     'Pins (Pico GP / ESP32 IO): 4 RLY_LATCH (GP2/IO48), 5 RLY_OE (GP3/IO47), 21 AUX (GP16/IO43), 22 SYNC_IN (GP17/IO44), '
                     '24 ADC_SYNC (GP18/IO0), 25 MOSI (GP19/IO1),\\n'
                     '26 MISO (GP20/IO2), 27 clock (GP21 GPOUT0/IO3), 29 SCK (GP22/IO15), 31 CS_ADC (GP26/IO18), 32 CS_DAC (GP27/IO16), '
                     '34 ADC_DRDY (GP28/IO17).\\n'
                     'J13 = external SPI master port (relays + HAT with the controller absent or held in reset).')
        elif v.startswith('J16: ADC/DAC sub-board'):
            t[1] = S(v.replace('J17: analog link to the sub-board (ADCn N tied to GND here).',
                               'J17: analog link to the sub-board; signals on the even pins, GND on the odd pins (ADCn N tied to GND here).'))
        elif v.startswith('ADC (on the HAT'):
            t[1] = S(v.replace('Clock: Pico GP21 8.000 MHz (R47 -> J16 pin 7) or the HAT oscillator.',
                               'Clock: Pico GP21 8.000 MHz (R47 -> J16 pin 7) or the HAT oscillator (needed with the ESP32-S3).'))
    s.save()



if __name__ == '__main__':
    main()

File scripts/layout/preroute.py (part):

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        track(b, n7, [pad_xy(b, cp, 1), xf(u, 5.3, -7.0), xf(u, 5.3, -1.27), xf(u, 3.81, -1.27)], 0.5)
        track(b, n4, [pad_xy(b, cn, 2), xf(u, -3.2, 5.45)], 0.5)

# ================================================================ SUM_HI: WE spine + bus
we = pad_xy(b, 'J7', 1)
u5in = pad_xy(b, 'U5', 2, smd=False)
assert abs(we[0] - u5in[0]) < 0.01
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for k in k_short:
    p = pad_xy(b, k, 7); track(b, 'IHI_OUT', [p, (p[0], yshort)], 0.4)

# ================================================================ RE input (U2 pin 3) and RE_BNC
r19a, r19b = pad_xy(b, 'R19', 1), pad_xy(b, 'R19', 2)
track(b, 'RE_IN', [r19b, pad_xy(b, 'U2', 3, smd=False)], 0.25)
k9 = pad_xy(b, 'K9', 7)
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    yb = place.ISLAND_Y                    # island: under the module, plus a tab at the bottom-left for JP5 pin 1
    zone('PICO_GND', lay, [(133.0, m), (159.3, m), (159.3, yb), (129.5, yb), (129.5, yb - 5.0), (133.0, yb - 5.0)], 1,
         name='Controller ground (joins GND via FB5/JP5 only)')
    # driven guard (RE_BUF = U2 output) around RE_IN: R19 pin2 -> U2 pin3 and its combo join
    ux = place.U2X
    zone('RE_BUF', lay, rect(ux - 4.53, 114.3, ux + 6.17, 126.2), 2, name='RE_BUF guard')
    # GUARD (U3-driven, J5 shell) around the RE_BNC run from K9 to R19/J5
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
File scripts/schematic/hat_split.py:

"""One-off: move the ADC/DAC to the pHAT sub-board (adc_hat/).

Deletes U20, U21 and their local support parts, prunes the wiring left dangling, and adds
J16 (2x20 socket, Raspberry Pi pinout) and J17 (2x6 analog socket) in their place.
"""
from redraw import *  # noqa
from redraw import _pt, _on

GONE = ['U20', 'JP4', 'R36', 'C24', 'C25', 'C26', 'U21', 'C54', 'C55', 'C56', 'C57', 'C58', 'C59',
        'X1', 'R35', 'JP6', 'R80', 'R81', 'R82', 'FB3', 'C10', '#FLG6']   # +3V3A has no loads left

# Raspberry Pi 40-pin header (J16) and analog link (J17); None = no connect
PI = {1: '+3V3D', 17: '+3V3D', 2: '+5V', 4: '+5V', 19: 'MOSI', 21: 'MISO', 23: 'SCK', 24: 'CS_ADC', 26: 'CS_DAC',
      7: 'HAT_CLK', 18: 'ADC_SYNC', 22: 'ADC_DRDY', **{n: 'GND' for n in (6, 9, 14, 20, 25, 30, 34, 39)}}
AN = {1: 'ADC0P', 3: 'ADC1P', 5: 'ADC2P', 7: 'ADC3P', 9: 'DAC_OUT', 11: 'DAC_REF',
      **{n: 'GND' for n in (2, 4, 6, 8, 10, 12)}}


def _pts(w):
    return [_pt(num(x[1]), num(x[2])) for x in find(find1(w, 'pts'), 'xy')]


def prune(s):
    """Remove dangling wire segments, then orphaned labels / power symbols / junctions / no-connects."""
    while True:
        pins = {_pt(*p) for sym in s.symbols() if not s.ref(sym).startswith('#PWR') for p in s.pins(s.ref(sym)).values()}
        named = {_pt(num(find1(l, 'at')[1]), num(find1(l, 'at')[2])) for l in s.items('label')}
        named |= {_pt(*s.at(sym)[:2]) for sym in s.symbols() if s.ref(sym).startswith('#PWR')}
        wires = [(w, _pts(w)) for w in s.items('wire')]
        ends = {}
        for _, (a, b) in wires:
            ends[a] = ends.get(a, 0) + 1; ends[b] = ends.get(b, 0) + 1

        def held(p, me):
            if p in pins or p in named or ends[p] > 1:
                return True
            return any(_on(p, a, b) for w, (a, b) in wires if w is not me)
        dead = [w for w, (a, b) in wires if not (held(a, w) and held(b, w))]
        if not dead:
            break
        for w in dead:
            s.remove(w)
    wires = [_pts(w) for w in s.items('wire')]
    touch = {p for sg in wires for p in sg} | pins

    def on_wire(p):
        return p in touch or any(_on(p, a, b) for a, b in wires)
    for l in s.items('label'):
        a = find1(l, 'at')
        if not on_wire(_pt(num(a[1]), num(a[2]))):
            s.remove(l)
    for sym in s.symbols():
        if s.ref(sym).startswith('#PWR') and not on_wire(_pt(*s.at(sym)[:2])):
            s.remove(sym)
    for nc in s.items('no_connect'):
        a = find1(nc, 'at')
        if _pt(num(a[1]), num(a[2])) not in pins:
            s.remove(nc)
    for j in s.items('junction'):
        a = find1(j, 'at'); p = _pt(num(a[1]), num(a[2]))
        n = sum(1 for sg in wires for q in sg if q == p) + sum(2 for a_, b_ in wires if _on(p, a_, b_)) + (p in pins)
        if n < 3:
            s.remove(j)


def relabel(s, old, new, near=None):
    for l in s.items('label'):
        if val(l) == old:
            a = find1(l, 'at')
            if near is None or (abs(num(a[1]) - near[0]) < 0.1 and abs(num(a[2]) - near[1]) < 0.1):
                l[1] = S(new)


def main():
    s = Sch()
    for r in GONE:
        s.remove(s.sym(r))
    prune(s)
    relabel(s, 'PICO_CLK', 'HAT_CLK')
    relabel(s, 'ADC_CLK', 'HAT_CLK')              # J13 pin 9
    for t in s.items('text'):
        v = val(t)
        if v.startswith(('ADC clock: JP6', 'X1 decoupling', 'U20 decoupling', 'U21 decoupling', 'R80-R82')):
            s.remove(t)

    FPI = 'Connector_PinSocket_2.54mm:PinSocket_2x20_P2.54mm_Vertical'
    FAN = 'Connector_PinSocket_2.54mm:PinSocket_2x06_P2.54mm_Vertical'
    s.add_symbol('Connector_Generic:Conn_02x20_Odd_Even', 'J16', 'ADC/DAC HAT (Pi 40-pin)', FPI, 210.82, 469.9, 0,
                 {'Note': 'Raspberry Pi header pinout; adc_hat sub-board plugs in here (or stacks on a Pi Zero)'})
    s.add_symbol('Connector_Generic:Conn_02x06_Odd_Even', 'J17', 'ADC/DAC HAT analog', FAN, 151.13, 482.6, 0,
                 {'Note': 'ADCn P/N pairs (N = GND here), DAC_OUT, DAC_REF'})
    b = Block(s, ['J16', 'J17'])
    b.F('J16', (212.09, 441.96), (212.09, 444.5), None)
    b.F('J17', (152.4, 472.44), (152.4, 474.98), None)
    for n in range(1, 41):
        net = PI.get(n)
        if net is None:
            b.nc('J16', n)
        else:
            b.term('J16', n, 2.54, net=net)
    for n, net in AN.items():
        b.term('J17', n, 2.54, net=net)
    b.finish(auto=False)
    s.text('J16: ADC/DAC sub-board (adc_hat/, Pi Zero pHAT outline). SPI0 = 19/21/23, CE0 24 = CS_ADC, CE1 26 = CS_DAC,\\n'
           'GPIO4 (7, GPCLK0) = HAT_CLK from Pico GP21 via R47, GPIO24 (18) = ADC_SYNC, GPIO25 (22) = ADC_DRDY.\\n'
           'J17: analog link to the sub-board (ADCn N tied to GND here).'.replace('\\n', '\n'), 129.54, 525.78)
    s.save()


if __name__ == '__main__':
    main()
